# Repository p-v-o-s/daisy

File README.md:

#daisy

## arrangement

# datalogger

Top:

Bottom:

- programmed via FTDI cable, board = "Arduino UNO"
- estimated < 100 microAmp sleep current
- DS1337 RTC with battery backup
- i2c EEPROM, 512KB storage
- RJ45 connector for 8-wire CAT-5,6,7 cable
- pin headers allow for patching RJ45 to digital / analog / power / ground
- JST header for battery power (or use remote)

# remote

Top:

Bottom:

- RJ45 connector
- JST header for battery power (or use remote)
- RJ45 pins broken out via header for custom patching
- 3 LEDs connected to ethernet pins 1,2,3 (if placed)
- 2 momentary buttons connected to ethernet pins 4,5 (if placed)
- mounting holes 

# remote w/ display

Replaces LEDs with a 128x32 OLED display from Adafruit:

Top:

Bottom:

To hook up [Adafruit OLED display](https://www.adafruit.com/products/931):

- 3.3V  OLED VIN.
- GND to OLED ground (GND).
- I2C SCL (A5) to OLED SCL.
- I2C SDA (A4) to OLED SDA.
- digital 4 to OLED RST.
- these pins are marked on the remote-display board.  Proper relevant patching must be done on the logger, to match.

# ref

http://pinouts.ru/NetworkCables/ethernet_10_100_1000_pinout.shtml

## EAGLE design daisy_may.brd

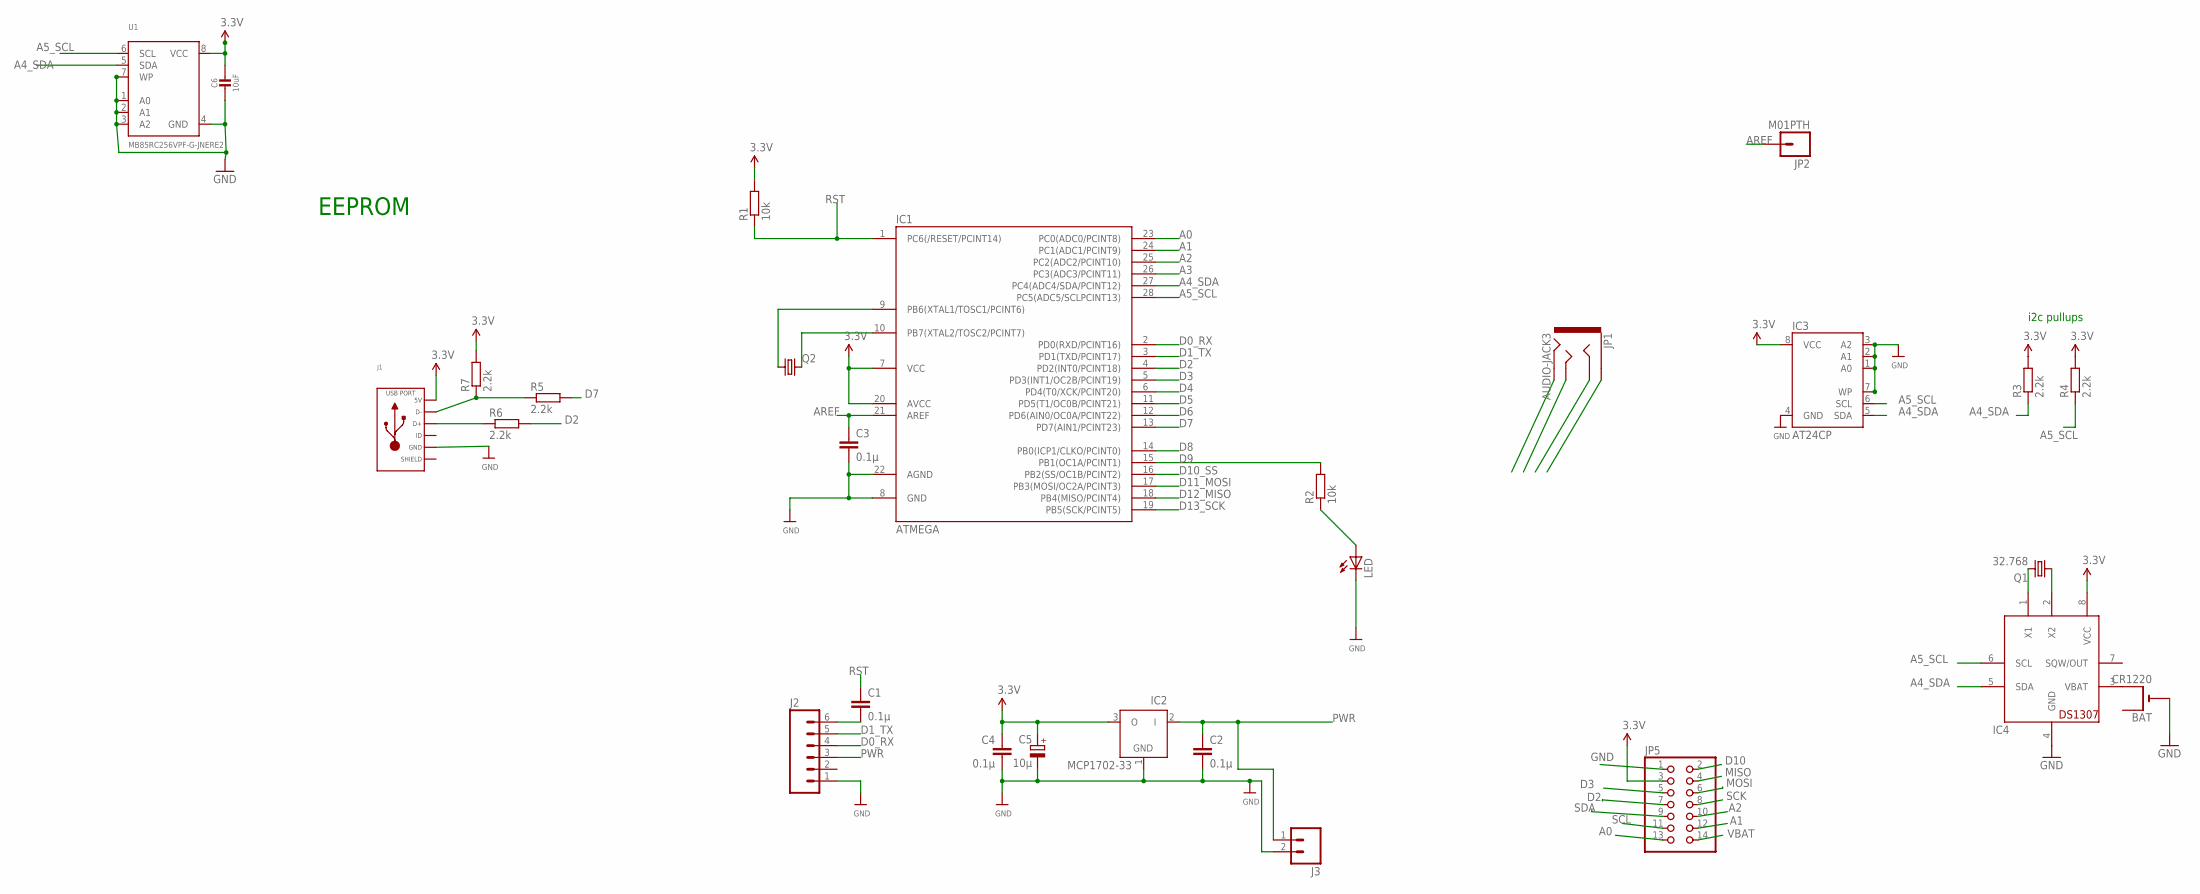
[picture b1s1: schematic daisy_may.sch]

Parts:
BAT: CR1220; CR1220-THM
C1, C2, C3, C4: 0.1µ; C025-024X044
C5: 10µ; E1,8-4
C6: 10uF; _0805MP
IC1: ATMEGA; DIL28-3
IC2: MCP1702-33; TO92
IC3: AT24CP; DIL08
IC4: DS1307; DIL08
J1: USB_MICRO_RIGHT; MICROUSB-RIGHT
J2: M06SILK_FEMALE_PTH; 1X06
J3: M02PTH; 1X02
JP1: AUDIO-JACK3; AUDIO-JACK-TRRS-SMD
JP2: M01PTH; 1X01
JP5: PINHD-2X7; 2X07
LED: LED3MM
Q1: 32.768; TC38H
Q2: CRYSTALHC49U70; HC49U70
R1, R2: 10k; 0204/7
R3, R4, R5, R6, R7: 2.2k; 0204/7
U1: MB85RC256VPF-G-JNERE2; SOIC8_208MIL

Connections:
A0: IC1.23 (PC0(ADC0/PCINT8)), JP5.13
A1: IC1.24 (PC1(ADC1/PCINT9)), JP5.12
A2: IC1.25 (PC2(ADC2/PCINT10)), JP5.10
A3: IC1.26 (PC3(ADC3/PCINT11))
A4_SDA: IC1.27 (PC4(ADC4/SDA/PCINT12)), IC3.5 (SDA), IC4.5 (SDA), R3.1, U1.5 (SDA)
A5_SCL: IC1.28 (PC5(ADC5/SCLPCINT13)), IC3.6 (SCL), IC4.6 (SCL), R4.1, U1.6 (SCL)
AREF: C3.1, IC1.21 (AREF), JP2.1
D0_RX: IC1.2 (PD0(RXD/PCINT16)), J2.4
D1_TX: IC1.3 (PD1(TXD/PCINT17)), J2.5
D2: IC1.4 (PD2(INT0/PCINT18)), JP5.7, R6.2
D3: IC1.5 (PD3(INT1/OC2B/PCINT19)), JP5.5
D4: IC1.6 (PD4(T0/XCK/PCINT20))
D5: IC1.11 (PD5(T1/OC0B/PCINT21))
D6: IC1.12 (PD6(AIN0/OC0A/PCINT22))
D7: IC1.13 (PD7(AIN1/PCINT23)), R5.2
D8: IC1.14 (PB0(ICP1/CLKO/PCINT0))
D9: IC1.15 (PB1(OC1A/PCINT1)), R2.2
D10: JP5.2
D10_SS: IC1.16 (PB2(SS/OC1B/PCINT2))
D11_MOSI: IC1.17 (PB3(MOSI/OC2A/PCINT3))
D12_MISO: IC1.18 (PB4(MISO/PCINT4))
D13_SCK: IC1.19 (PB5(SCK/PCINT5))
GND: BAT.-, C2.2, C3.2, C4.2, C5.-, C6.2, IC1.8 (GND), IC1.22 (AGND), IC2.1 (GND), IC3.1 (A0), IC3.2 (A1), IC3.3 (A2), IC3.4 (GND), IC3.7 (WP), IC4.4 (GND), J2.1, J3.2, JP5.1, LED.K (C), U1.1 (A0), U1.2 (A1), U1.3 (A2), U1.4 (GND), U1.7 (WP)
MISO: JP5.4
MOSI: JP5.6
unnamed: IC1.9 (PB6(XTAL1/TOSC1/PCINT6)), Q2.1
unnamed: LED.A, R2.1
unnamed: J1.2 (D-), R5.1, R7.1
unnamed: J1.3 (D+), R6.1
unnamed: IC4.1 (X1), Q1.2
unnamed: IC4.2 (X2), Q1.1
unnamed: C1.2, J2.6
unnamed: IC1.10 (PB7(XTAL2/TOSC2/PCINT7)), Q2.2
unnamed: BAT.+2 (+1), IC4.3 (VBAT)
PWR: C2.1, IC2.2 (I), J2.3, J3.1
RST: C1.1, IC1.1 (PC6(/RESET/PCINT14)), R1.1
SCK: JP5.8
SCL: JP5.11
SDA: JP5.9
SLD: J1.S1 (SLD), J1.S2 (SLD), J1.S3 (SLD), J1.S4 (SLD), J1.S5 (SLD), J1.S6 (SLD), J1.S7 (SLD), J1.S8 (SLD)
VBAT: JP5.14
VCC: C4.1, C5.+, C6.1, IC1.7 (VCC), IC1.20 (AVCC), IC2.3 (O), IC3.8 (VCC), IC4.8 (VCC), J1.1 (5V), JP5.3, R1.2, R3.2, R4.2, R7.2, U1.8 (VCC)

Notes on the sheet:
i2c pullups
EEPROM

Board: 2 copper layers, 28 parts (2 on the bottom side), 26 nets, no tracks yet.

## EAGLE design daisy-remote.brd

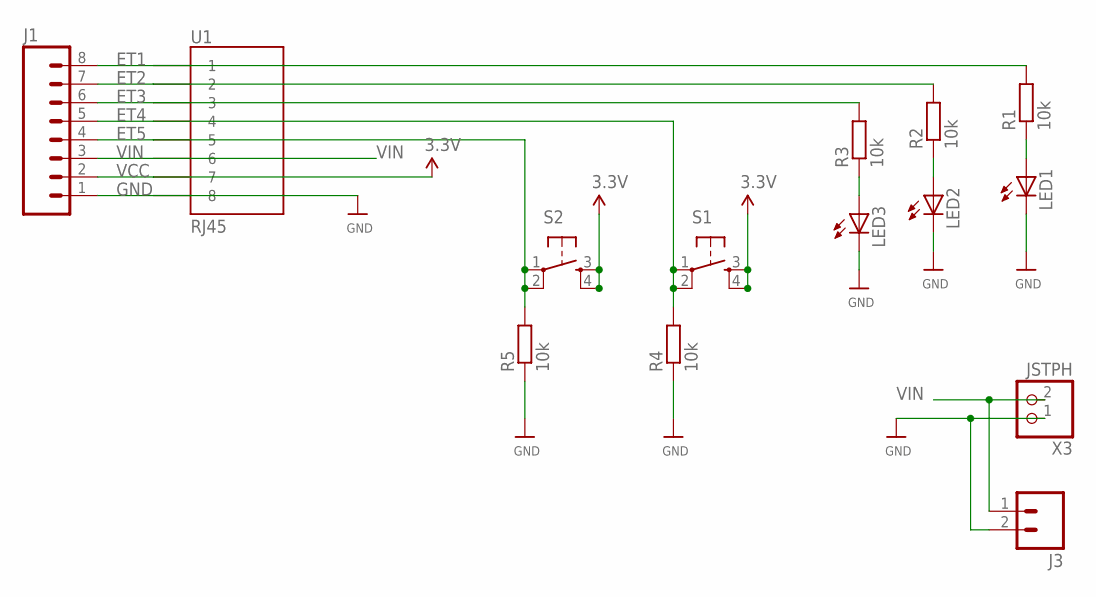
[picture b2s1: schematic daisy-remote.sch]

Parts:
J1: M08; 1X08_ROUND
J3: M02PTH; 1X02
LED1, LED2, LED3: LED5MM
R1, R2, R3, R4, R5: 10k; 0204/7
S1, S2: TAC_SWITCHPTH; TACTILE-PTH
U1: RJ45; RJ45-8
X3: JSTPH; JSTPH2

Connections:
ET1: J1.8, R1.2, U1.1
ET2: J1.7, R2.2, U1.2
ET3: J1.6, R3.2, U1.3
ET4: J1.5, R4.2, S1.1, S1.2, U1.4
ET5: J1.4, R5.2, S2.1, S2.2, U1.5
GND: J1.1, J3.2, LED1.K (C), LED2.K (C), LED3.K (C), R4.1, R5.1, U1.8, X3.1
unnamed: LED1.A, R1.1
unnamed: LED2.A, R2.1
unnamed: LED3.A, R3.1
VCC: J1.2, S1.3, S1.4, S2.3, S2.4, U1.7
VIN: J1.3, J3.1, U1.6, X3.2

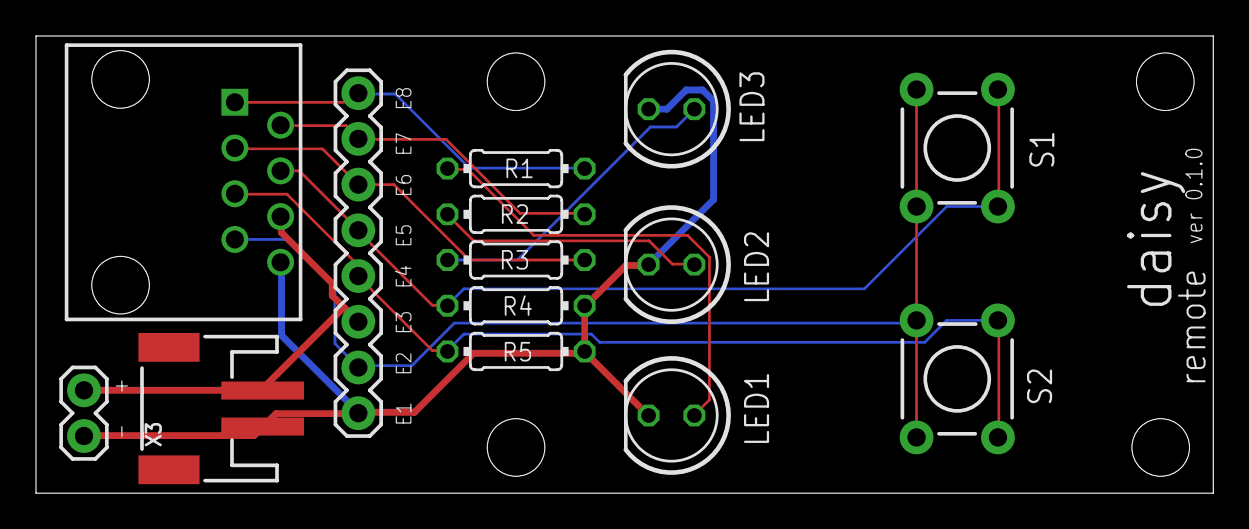
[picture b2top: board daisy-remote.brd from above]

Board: 2 copper layers, 65.4 x 25.4 mm, 14 parts (0 on the bottom side), 11 nets.

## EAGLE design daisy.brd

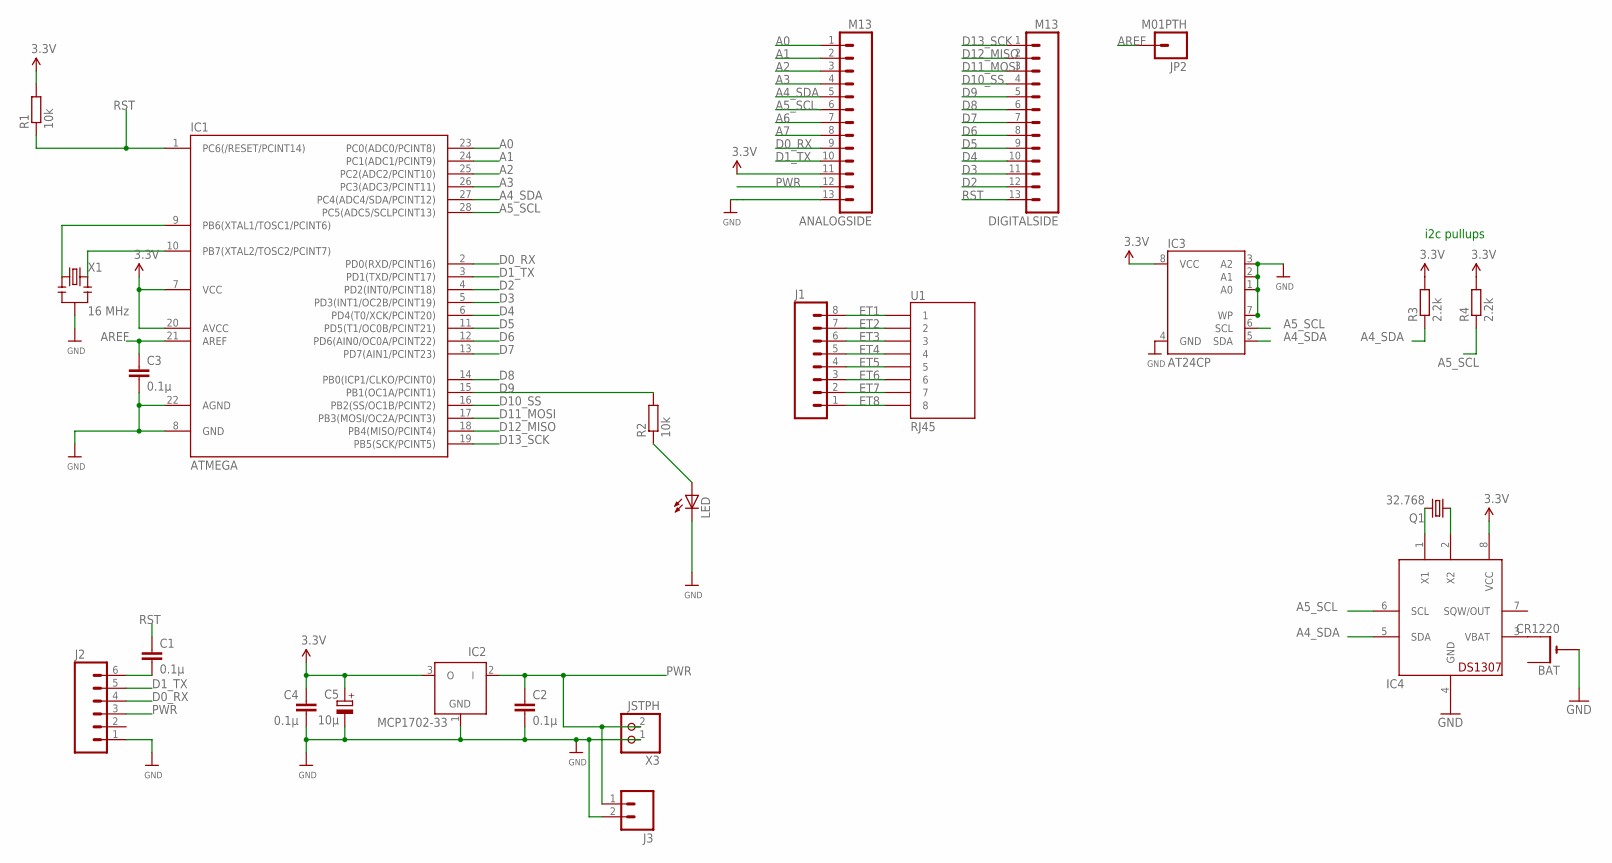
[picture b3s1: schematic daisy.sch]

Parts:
ANALOGSIDE: M13; 1X13
BAT: CR1220; CR1220-THM
C1, C2, C3, C4: 0.1µ; C025-024X044
C5: 10µ; E1,8-4
DIGITALSIDE: M13; 1X13
IC1: ATMEGA; DIL28-3
IC2: MCP1702-33; TO92
IC3: AT24CP; DIL08
IC4: DS1307; DIL08
J1: M08; 1X08_ROUND
J2: M06SILK_FEMALE_PTH; 1X06
J3: M02PTH; 1X02
JP2: M01PTH; 1X01
LED: LED3MM
Q1: 32.768; TC38H
R1, R2: 10k; 0204/7
R3, R4: 2.2k; 0204/7
U1: RJ45; RJ45-8
X1: 16 MHz; RESONATOR-PTH
X3: JSTPH; JSTPH2

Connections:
A0: ANALOGSIDE.1, IC1.23 (PC0(ADC0/PCINT8))
A1: ANALOGSIDE.2, IC1.24 (PC1(ADC1/PCINT9))
A2: ANALOGSIDE.3, IC1.25 (PC2(ADC2/PCINT10))
A3: ANALOGSIDE.4, IC1.26 (PC3(ADC3/PCINT11))
A4_SDA: ANALOGSIDE.5, IC1.27 (PC4(ADC4/SDA/PCINT12)), IC3.5 (SDA), IC4.5 (SDA), R3.1
A5_SCL: ANALOGSIDE.6, IC1.28 (PC5(ADC5/SCLPCINT13)), IC3.6 (SCL), IC4.6 (SCL), R4.1
A6: ANALOGSIDE.7
A7: ANALOGSIDE.8
AREF: C3.1, IC1.21 (AREF), JP2.1
D0_RX: ANALOGSIDE.9, IC1.2 (PD0(RXD/PCINT16)), J2.4
D1_TX: ANALOGSIDE.10, IC1.3 (PD1(TXD/PCINT17)), J2.5
D2: DIGITALSIDE.12, IC1.4 (PD2(INT0/PCINT18))
D3: DIGITALSIDE.11, IC1.5 (PD3(INT1/OC2B/PCINT19))
D4: DIGITALSIDE.10, IC1.6 (PD4(T0/XCK/PCINT20))
D5: DIGITALSIDE.9, IC1.11 (PD5(T1/OC0B/PCINT21))
D6: DIGITALSIDE.8, IC1.12 (PD6(AIN0/OC0A/PCINT22))
D7: DIGITALSIDE.7, IC1.13 (PD7(AIN1/PCINT23))
D8: DIGITALSIDE.6, IC1.14 (PB0(ICP1/CLKO/PCINT0))
D9: DIGITALSIDE.5, IC1.15 (PB1(OC1A/PCINT1)), R2.2
D10_SS: DIGITALSIDE.4, IC1.16 (PB2(SS/OC1B/PCINT2))
D11_MOSI: DIGITALSIDE.3, IC1.17 (PB3(MOSI/OC2A/PCINT3))
D12_MISO: DIGITALSIDE.2, IC1.18 (PB4(MISO/PCINT4))
D13_SCK: DIGITALSIDE.1, IC1.19 (PB5(SCK/PCINT5))
ET1: J1.8, U1.1
ET2: J1.7, U1.2
ET3: J1.6, U1.3
ET4: J1.5, U1.4
ET5: J1.4, U1.5
ET6: J1.3, U1.6
ET7: J1.2, U1.7
ET8: J1.1, U1.8
GND: ANALOGSIDE.13, BAT.-, C2.2, C3.2, C4.2, C5.-, IC1.8 (GND), IC1.22 (AGND), IC2.1 (GND), IC3.1 (A0), IC3.2 (A1), IC3.3 (A2), IC3.4 (GND), IC3.7 (WP), IC4.4 (GND), J2.1, J3.2, LED.K (C), X1.2, X3.1
unnamed: IC1.9 (PB6(XTAL1/TOSC1/PCINT6)), X1.1
unnamed: LED.A, R2.1
unnamed: IC4.1 (X1), Q1.2
unnamed: IC4.2 (X2), Q1.1
unnamed: C1.2, J2.6
unnamed: IC1.10 (PB7(XTAL2/TOSC2/PCINT7)), X1.3
unnamed: BAT.+2 (+1), IC4.3 (VBAT)
PWR: ANALOGSIDE.12, C2.1, IC2.2 (I), J2.3, J3.1, X3.2
RST: C1.1, DIGITALSIDE.13, IC1.1 (PC6(/RESET/PCINT14)), R1.1
VCC: ANALOGSIDE.11, C4.1, C5.+, IC1.7 (VCC), IC1.20 (AVCC), IC2.3 (O), IC3.8 (VCC), IC4.8 (VCC), R1.2, R3.2, R4.2

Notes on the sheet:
i2c pullups

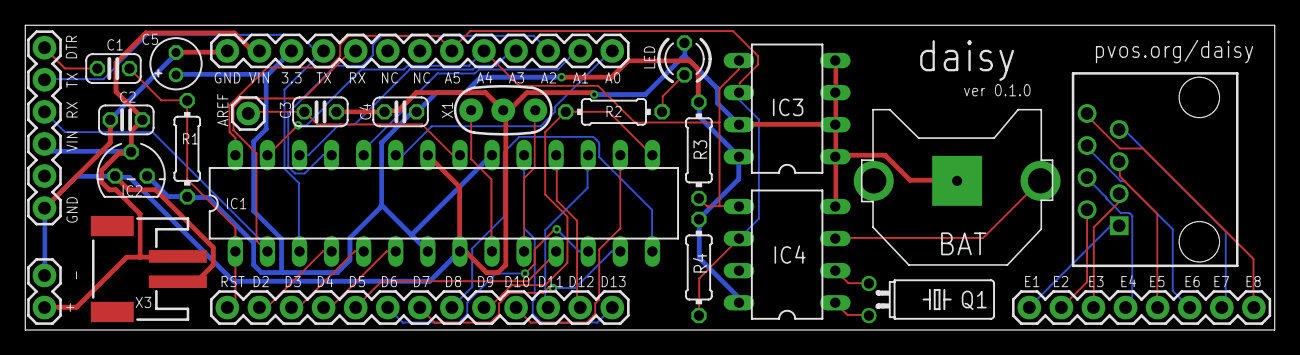
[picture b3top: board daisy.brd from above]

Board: 2 copper layers, 98.9 x 24.1 mm, 25 parts (0 on the bottom side), 40 nets.

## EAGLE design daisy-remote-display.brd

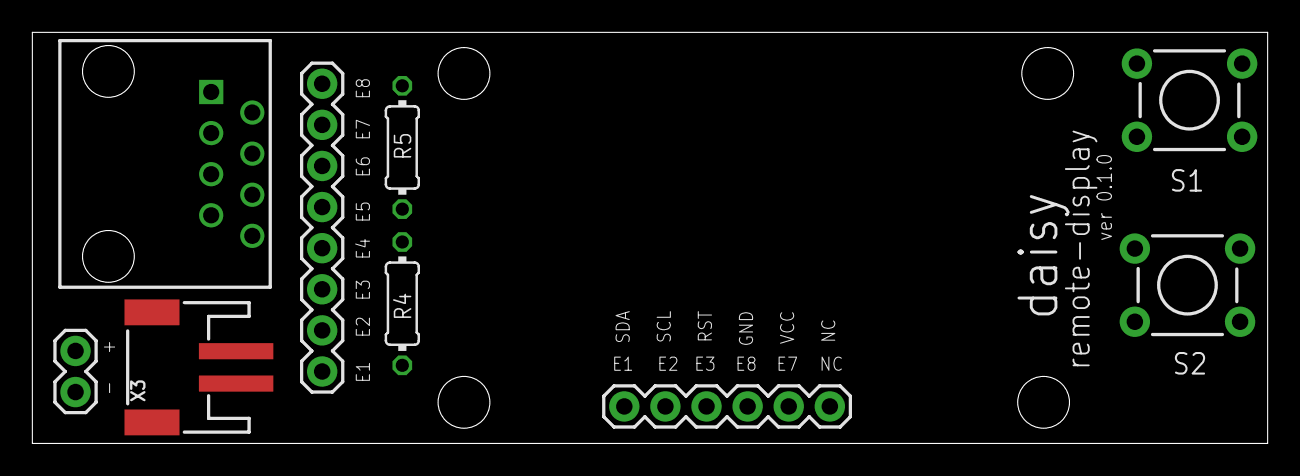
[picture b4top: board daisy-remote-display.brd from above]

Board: 2 copper layers, 76.3 x 25.4 mm, 9 parts (0 on the bottom side), 8 nets, no tracks yet.

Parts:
J1: 1X08_ROUND
J3: 1X02
J4: 1X06
R4, R5: 10k; 0204/7
S1, S2: TACTILE-PTH
U1: RJ45; RJ45-8
X3: JSTPH; JSTPH2

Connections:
A4_SDA: J1.8, J4.1, U1.1
A5_SCL: J1.7, J4.2, U1.2
ET4: J1.5, R4.2, S1.1, S1.2, U1.4
ET5: J1.4, R5.2, S2.1, S2.2, U1.5
GND: J1.1, J3.2, J4.4, R4.1, R5.1, U1.8, X3.1
RST: J1.6, J4.3, U1.3
VCC: J1.2, J4.5, S1.3, S1.4, S2.3, S2.4, U1.7
VIN: J1.3, J3.1, U1.6, X3.2

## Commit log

2016-09-07 upate

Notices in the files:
parts and their libraries:
SparkFun-Connectors: Licensing: CC v3.0 Share-Alike You are welcome to use this library for commercial purposes.
SparkFun-Retired: Licensing:Creative Commons ShareAlike 4.0 International - https://creativecommons.org/licenses/by-sa/4.0
